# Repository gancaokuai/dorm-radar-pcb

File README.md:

# Dorm Radar PCB

ESP32-C3 based local motion-alert PCB project. The system uses an LD2450 radar on the transmitter board and a local LED on the receiver board. Communication uses ESP-NOW. No camera, microphone, cloud service, or charging circuit is included.

## Boards

- TX board: 70 mm x 42 mm, LD2450 interface and ESP-NOW transmitter
- RX board: 68 mm x 42 mm, ESP-NOW receiver and LED indicator

## Hardware

- ESP32-C3-WROOM-02
- LD2450 24 GHz radar module
- MT3608 5 V boost converter
- AP2112K-3.3 regulator
- External protected 1S 18650 battery pack
- Two-layer PCB with bottom ground plane

## Repository Layout

```text
hardware/kicad/DormRadar/
  DormRadar.kicad_pro
  DormRadar.kicad_sch
  generate_schematic.py
  generate_pcbs.py
  release/
    BOM_common.csv
    BOM_TX.csv
    BOM_RX.csv
    TX/
      DormRadar_TX.kicad_pcb
      DRC.txt
      gerber/
      drill/
      position/
    RX/
      DormRadar_RX.kicad_pcb
      DRC.txt
      gerber/
      drill/
      position/
```

## Firmware

The initial ESP32-C3 firmware MVP is in `firmware/`.

- TX reads the LD2450 radar and sends detection state over ESP-NOW.
- RX validates the packet and drives the local LED.
- The build script uses `F:\DormRadar` as an ASCII junction because the ESP32 GCC toolchain cannot resolve the Chinese project path.
- Build with `F:\防宿管雷达\firmware\build.ps1 all`.

See `firmware/README.md` for pin mapping, thresholds, and first-board bring-up steps.
## Verification

- TX: 0 unconnected pads, 0 electrical errors
- RX: 0 unconnected pads, 0 electrical errors
- Remaining DRC items are silkscreen-only warnings caused by the ESP32 antenna overhang and local reference text placement.
- Freerouting 2.4.1 was used in single-thread mode, then all tracks below 0.20 mm were normalized to at least 0.20 mm.

## Notes

Use this design only in compliance with local rules and do not modify fire, access-control, or safety equipment. The radar should have direct line of sight to the intended detection zone.

## Licensing

This is a multi-licensed project. Firmware is under Apache-2.0, hardware design files are under CERN-OHL-W-2.0, and documentation is under CC BY-SA 4.0. See LICENSING.md and LICENSES/ for details.

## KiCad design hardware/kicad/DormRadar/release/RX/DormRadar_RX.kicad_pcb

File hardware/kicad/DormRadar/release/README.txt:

防宿管雷达 PCB 发布说明
日期: 2026-09-12
KiCad: 10.0.6

板卡:
- TX: 70 mm x 42 mm, 包含 LD2450 接口和 ESP-NOW 发射端
- RX: 68 mm x 42 mm, 仅包含 ESP-NOW 接收端和 LED

设计要点:
- ESP32-C3-WROOM-02 天线区悬出板边，减少 PCB 尺寸并保持天线净空
- 1S 18650 电池输入，无充电功能
- MT3608 升压到 5V
- AP2112K-3.3 给 ESP32 供电
- 双层板，底层 GND 铺铜
- Freerouting 2.4.1 自动布线，单线程模式
- 最终 DRC: 0 个未连接焊盘，0 个电气错误，剩余仅为丝印边缘提示

生产文件:
- TX/gerber, TX/drill, TX/position
- RX/gerber, RX/drill, RX/position
- BOM_common.csv
- TX/DormRadar_TX.kicad_pcb
- RX/DormRadar_RX.kicad_pcb

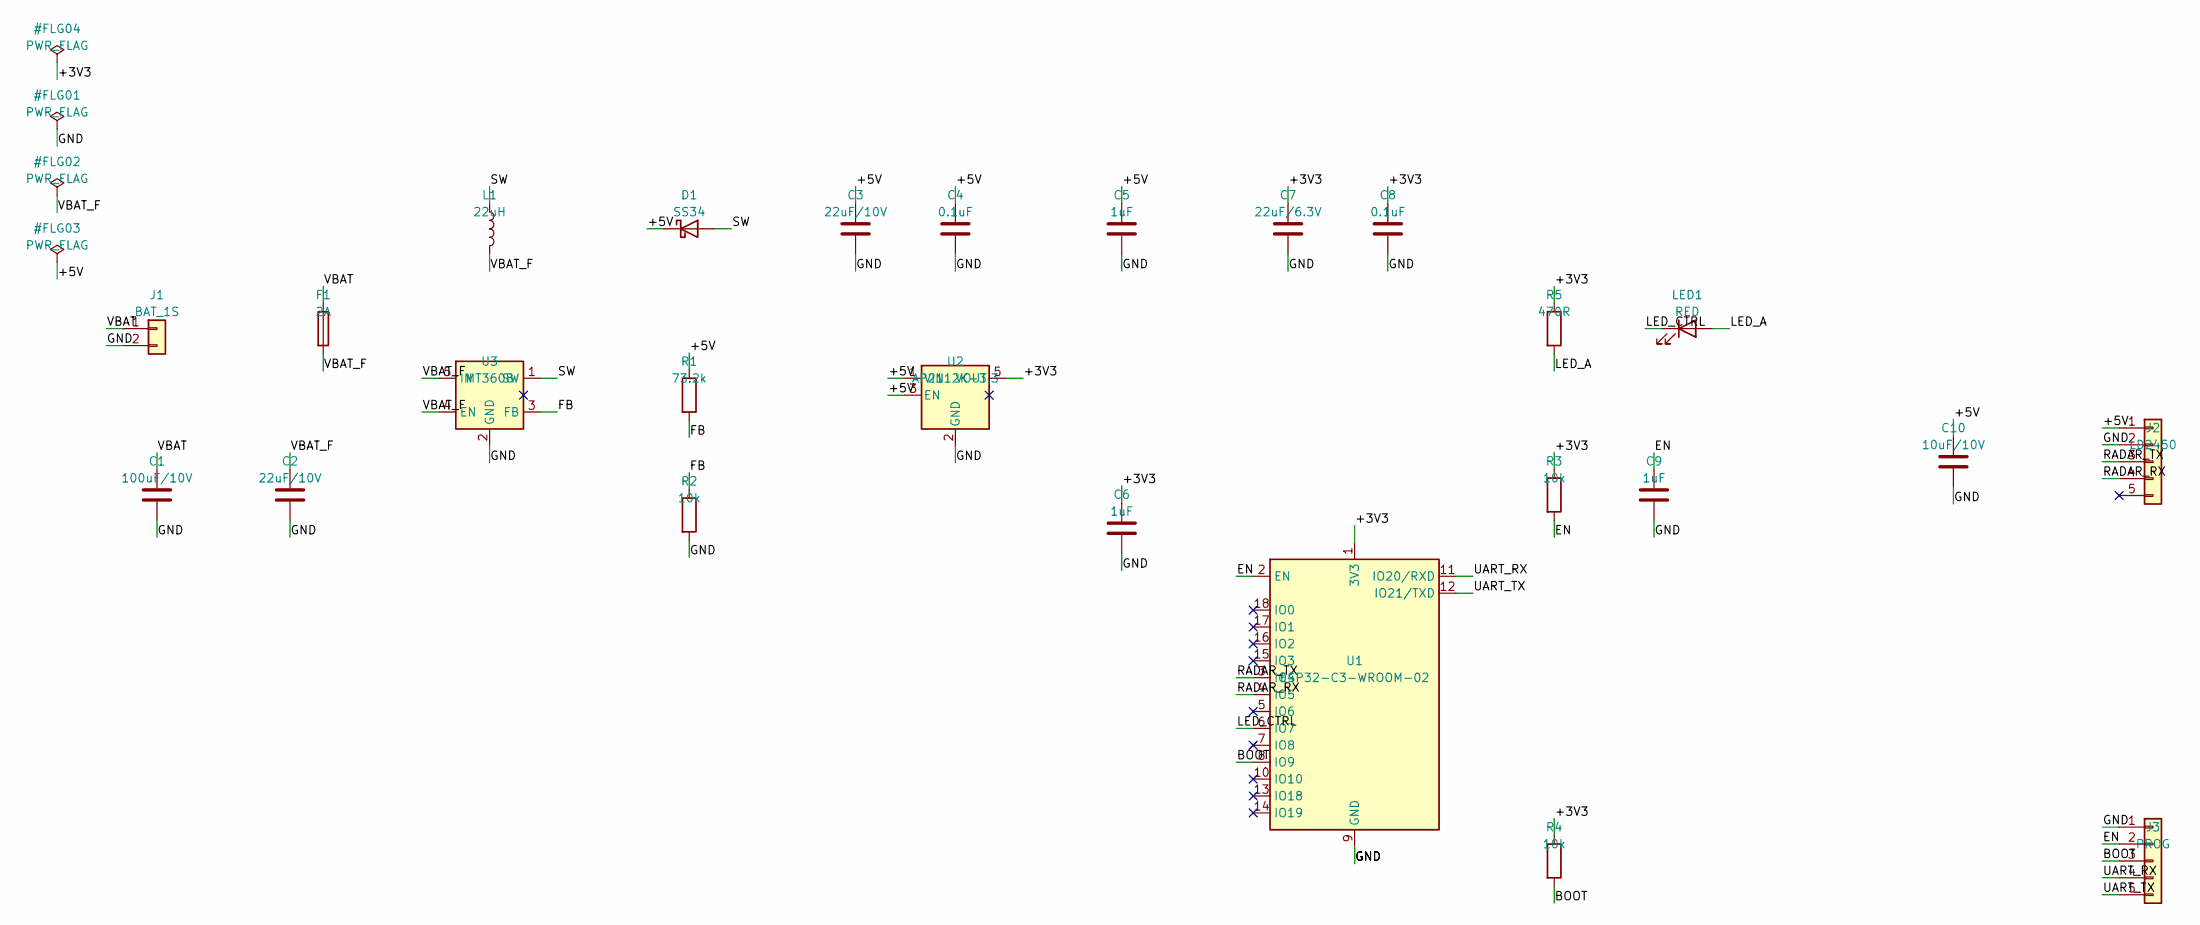
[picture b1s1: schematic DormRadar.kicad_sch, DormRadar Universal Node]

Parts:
C1: 100uF/10V; C_1210_3225Metric
C2, C3: 22uF/10V; C_1206_3216Metric
C4, C8: 0.1uF; C_0603_1608Metric
C5, C6, C9: 1uF; C_0805_2012Metric
C7: 22uF/6.3V; C_1206_3216Metric
C10: 10uF/10V; C_0805_2012Metric
D1: SS34; D_SMA
F1: 2A; Fuse_1206_3216Metric
J1: BAT_1S; JST_VH_B2P-VH-B_1x02_P3.96mm_Vertical
J2: LD2450; PinHeader_1x05_P1.27mm_Vertical
J3: PROG; PinHeader_1x05_P2.54mm_Vertical
L1: 22uH; L_12x12mm_H4.5mm
LED1: RED; LED_0805_2012Metric
R1: 73.2k; R_0805_2012Metric
R2, R3, R4: 10k; R_0805_2012Metric
R5: 470R; R_0805_2012Metric
U1: ESP32-C3-WROOM-02
U2: AP2112K-3.3; SOT-23-5
U3: MT3608; SOT-23-6

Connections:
+3V3: C6.1, C7.1, C8.1, R3.1, R4.1, R5.1, U1.1 (3V3), U2.5
+5V: C3.1, C4.1, C5.1, C10.1, D1.1 (K), J2.1, R1.1, U2.1, U2.3
BOOT: J3.3, R4.2, U1.8 (IO9)
EN: C9.1, J3.2, R3.2, U1.2 (EN)
FB: R1.2, R2.1, U3.3 (FB)
GND: C1.2, C2.2, C3.2, C4.2, C5.2, C6.2, C7.2, C8.2, C9.2, C10.2, J1.2, J2.2, J3.1, R2.2, U1.9 (GND), U1.19 (GND), U2.2, U3.2 (GND)
LED_A: LED1.2 (A), R5.2
LED_CTRL: LED1.1 (K), U1.6 (IO7)
RADAR_RX: J2.4, U1.4 (IO5)
RADAR_TX: J2.3, U1.3 (IO4)
SW: D1.2 (A), L1.1, U3.1 (SW)
UART_RX: J3.4, U1.11 (IO20/RXD)
UART_TX: J3.5, U1.12 (IO21/TXD)
VBAT: C1.1, F1.1, J1.1
VBAT_F: C2.1, F1.2, L1.2, U3.4 (EN), U3.5 (IN)

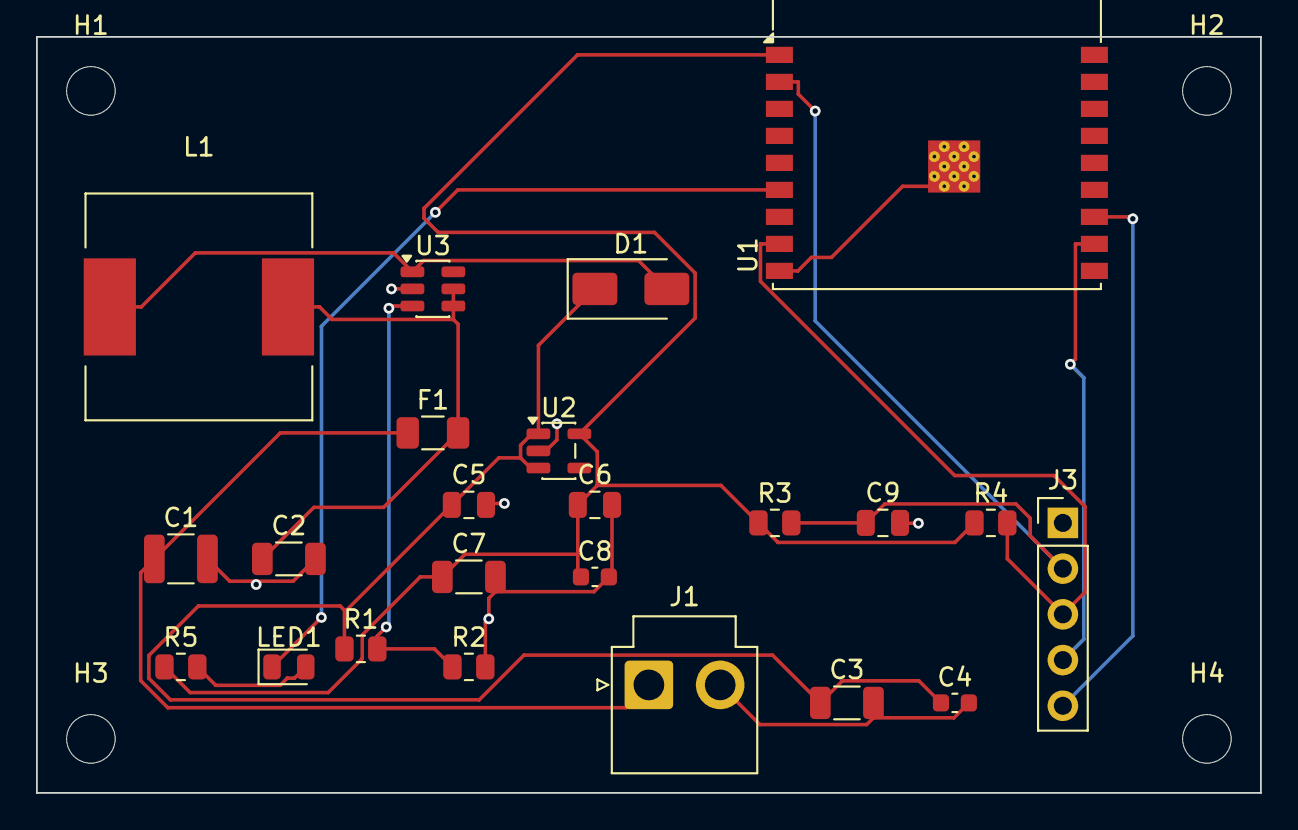
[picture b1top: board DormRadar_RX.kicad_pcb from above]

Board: 2 copper layers, 68.0 x 42.0 mm, 27 parts (0 on the bottom side), 13 nets.

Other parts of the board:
H1, H2, H3, H4: M2.5; MountingHole_2.7mm_M2.5

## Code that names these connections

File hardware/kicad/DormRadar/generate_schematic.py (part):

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    {"lib":"Device","symbol":"R","ref":"R5","value":"470R","footprint":"Resistor_SMD:R_0805_2012Metric","at":(240,50),"nets":{"1":"+3V3","2":"LED_A"}},
    {"lib":"Device","symbol":"LED","ref":"LED1","value":"RED","footprint":"LED_SMD:LED_0805_2012Metric","at":(260,50),"nets":{"1":"LED_CTRL","2":"LED_A"}},
    {"lib":"Device","symbol":"C","ref":"C10","value":"10uF/10V","footprint":"Capacitor_SMD:C_0805_2012Metric","at":(300,70),"nets":{"1":"+5V","2":"GND"}},
    {"lib":"Connector_Generic","symbol":"Conn_01x05","ref":"J2","value":"LD2450","footprint":"Connector_PinHeader_1.27mm:PinHeader_1x05_P1.27mm_Vertical","at":(330,70),"nets":{"1":"+5V","2":"GND","3":"RADAR_TX","4":"RADAR_RX","5":None}},
    {"lib":"Connector_Generic","symbol":"Conn_01x05","ref":"J3","value":"PROG","footprint":"Connector_PinHeader_2.54mm:PinHeader_1x05_P2.54mm_Vertical","at":(330,130),"nets":{"1":"GND","2":"EN","3":"BOOT","4":"UART_RX","5":"UART_TX"}},
    {"lib":"power","symbol":"PWR_FLAG","ref":"#FLG01","value":"PWR_FLAG","footprint":"","at":(15,20),"nets":{"1":"GND"}},
    {"lib":"power","symbol":"PWR_FLAG","ref":"#FLG02","value":"PWR_FLAG","footprint":"","at":(15,30),"nets":{"1":"VBAT_F"}},
    {"lib":"power","symbol":"PWR_FLAG","ref":"#FLG03","value":"PWR_FLAG","footprint":"","at":(15,40),"nets":{"1":"+5V"}},
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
